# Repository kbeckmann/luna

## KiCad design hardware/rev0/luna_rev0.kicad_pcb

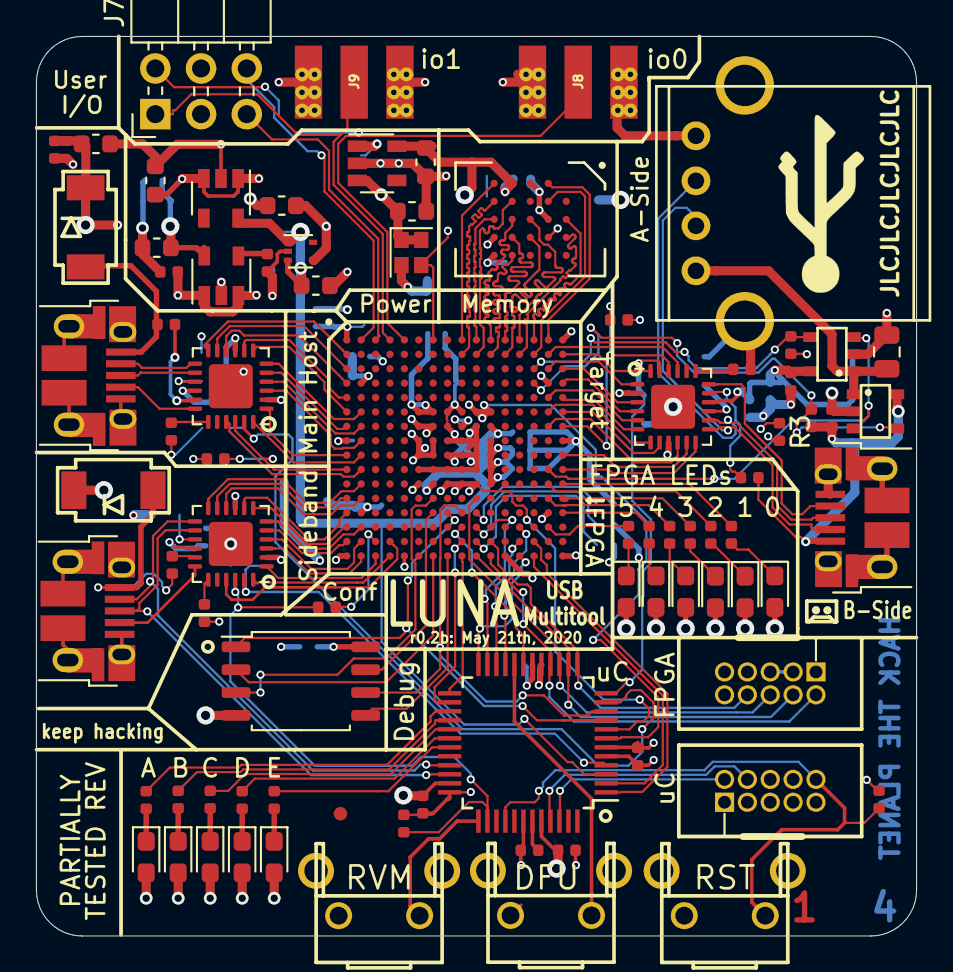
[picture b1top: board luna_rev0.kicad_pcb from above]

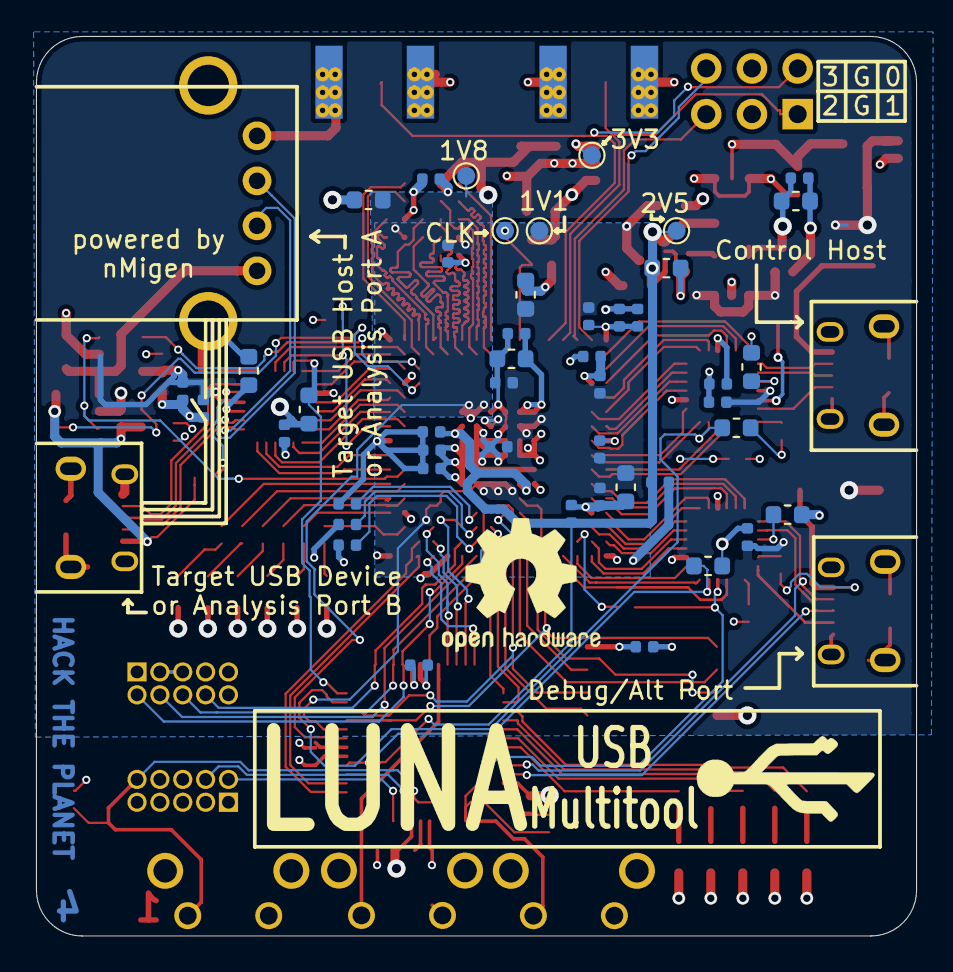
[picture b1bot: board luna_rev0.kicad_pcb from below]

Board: 4 copper layers, 48.9 x 50.0 mm, 128 parts (46 on the bottom side), 143 nets.

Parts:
C1, C2, C3, C4, C6, C20, C21: 2.2uF; C_0603_1608Metric
C5, C19, C22, C28, C29, C30, C36, C37, C42, C43, C48, C50: 1uF; C_0603_1608Metric
C7, C8, C9, C10, C11, C12, C13, C14, C15, C16, C17, C18, C23, C24, C25, C26, C27, C31, C32, C33, C34, C35, C38, C39, C40, C41, C44, C45, C46, C47, C49, C51, C54, C55: 0.1uF; C_0402_1005Metric
C52: 470pF; C_0402_1005Metric
C53: 10uF; C_0805_2012Metric
D1, D8: PMEG3050EP,115; SOD128
D2: RED; LED_0603_1608Metric_Pad1.05x0.95mm_HandSolder
D3: ORANGE; LED_0603_1608Metric_Pad1.05x0.95mm_HandSolder
D4: YELLOW; LED_0603_1608Metric_Pad1.05x0.95mm_HandSolder
D5: GREEN; LED_0603_1608Metric_Pad1.05x0.95mm_HandSolder
D6, D10, D14: BLUE; LED_0603_1608Metric_Pad1.05x0.95mm_HandSolder
D7: PURPLE; LED_0603_1608Metric_Pad1.05x0.95mm_HandSolder
D11, D13: PINK; LED_0603_1608Metric_Pad1.05x0.95mm_HandSolder
D12: WHITE; LED_0603_1608Metric_Pad1.05x0.95mm_HandSolder
FID: Fiducial_0.75mm_Mask2.25mm
IC1: ECP5-BGA256; lattice_cabga256
J1, J2, J4: USB_B_Micro; USB_Micro-B_Amphenol_10103594-0001LF_Horizontal
J3: USB_A; CONN-Amphenol-UE27AC54100
J5, J6: Conn_ARM_JTAG_SWD_10; SWD_CONNECTOR_LARGE_BOX
J7: Conn_02x02_Counter_Clockwise; PinHeader_2x03_P2.54mm_Horizontal
J8, J9: Conn_Coaxial; SMA-EDGE
R1, R2, R3, R12, R13, R14, R23, R24, R25: 10K; R_0402_1005Metric
R7, R8, R9, R10, R11, R26, R27, R28, R29, R30, R31: 330; R_0402_1005Metric
R15: 1K; R_0402_1005Metric
R16, R18, R20: 8.06k+1%; R_0402_1005Metric
R17, R19, R21: 20K; R_0402_1005Metric
R22: 15K; R_0402_1005Metric
SW1: BTN_RECOVERY; SWITCH-FSMRA
SW2: BTN_DFU; SWITCH-FSMRA
SW3: BTN_RESET; SWITCH-FSMRA
TP1, TP2, TP3, TP4, TP5: TestPoint; TestPoint_Pad_D1.0mm
U1, U12: AP22814-SOT; SOT25
U2: MIC5504-1.8YM5; SOT-23-5
U3: MIC5219-3.3YM5; SOT-23-5
U4: TCR2EE11; SOT-553
U5: MIC5504-2.5YM5; SOT-23-5
U6: ATSAMD21G18A-AUT; TQFP-48_7x7mm_P0.5mm
U7: W25Q32JVSS; SOIC-8_5.23x5.23mm_P1.27mm
U8, U9, U11: USB3343; VQFN-24-1EP_4x4mm_P0.5mm_EP2.45x2.45mm
U10: S27KS0641; BGA-24_5x5_6.0x8.0mm
Y1: DSC60xx; Crystal_SMD_2016-4Pin_2.0x1.6mm

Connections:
+1V1: C1.1, C3.1, C7.1, C9.1, C11.1, C13.1, C15.1, C17.1, C29.1, IC1.G6, IC1.G7, IC1.G9, IC1.L8, IC1.L9, IC1.L10, TP4.1, U4.4, U6.8
+1V8: C19.1, C21.1, C23.1, C25.1, IC1.F10, IC1.F11, TP2.1, U2.5, U6.7, U10.B4, U10.D1, U10.E4
+2V5: C22.1, C24.1, C26.1, C27.1, C30.1, IC1.G11, IC1.L7, TP5.1, U4.1, U4.3, U5.5, U6.3
+3V3: C2.1, C4.1, C5.1, C8.1, C10.1, C12.1, C14.1, C16.1, C18.1, C20.1, C28.1, C31.1, C32.1, C33.1, C34.1, C35.1, C39.1, C41.1, C49.1, D2.2, D3.2, D4.2, D5.2, D6.2, D7.2, D10.2, D11.2, D12.2, D13.2, D14.2, IC1.F6, IC1.F7, IC1.H6, IC1.H7, IC1.H11, IC1.J6, IC1.J7, IC1.J11, IC1.K11, IC1.L6, IC1.L11, J5.1, J6.1, R3.1, R13.2, R22.2, R23.2, R24.2, R25.1, TP3.1, U2.1, U2.3, U3.5, U5.1, U5.3, U6.6, U6.17, U6.36, U6.44, U7.8, U8.2, U8.9, U9.2, U9.9, U11.2, U11.9, Y1.1, Y1.4
+5V: C6.1, C38.1, C40.1, C44.1, C45.1, C46.1, C47.1, C54.1, D1.1, D8.1, U1.5, U3.1, U3.3, U8.16, U9.16, U11.16
/DEBUG_SPI_CLK: IC1.R13, U6.22
/DEBUG_SPI_CS: IC1.T13, U6.24
/DEBUG_SPI_MISO: IC1.P11, U6.23
/DEBUG_SPI_MOSI: IC1.P13, U6.21
/Debug & Control Connections/CLKIN_60MHZ: IC1.A7, TP1.1, Y1.3
/Debug & Control Connections/USER_IO0: IC1.A5, J7.2, J8.1
/Debug & Control Connections/USER_IO1: IC1.A4, J7.1, J9.1
/Debug & Control Connections/USER_IO2: IC1.A3, J7.5
/Debug & Control Connections/USER_IO3: IC1.A2, J7.6
/FORCE_DFU: SW2.2, U6.20
/FORCE_RECOVERY: SW1.2, U6.37
/FPGA Configuration and Dev Features/D0: IC1.T8, U7.5
/FPGA Configuration and Dev Features/D1: IC1.T7, U7.2
/FPGA Configuration and Dev Features/D2: IC1.M7, U7.3
/FPGA Configuration and Dev Features/D3: IC1.N7, U7.7
/FPGA Configuration and Dev Features/FPGA_CFG0: IC1.N10, R12.1
/FPGA Configuration and Dev Features/FPGA_CFG1: IC1.P10, R13.1
/FPGA Configuration and Dev Features/FPGA_CFG2: IC1.R10, R14.1
/FPGA Configuration and Dev Features/FPGA_CONFIG_CLK: IC1.N9, U6.10, U7.6
/FPGA Configuration and Dev Features/FPGA_DONE: IC1.P9, U6.19
/FPGA Configuration and Dev Features/FPGA_TCK: IC1.T10, J5.4, U6.14
/FPGA Configuration and Dev Features/FPGA_TDI: IC1.R11, J5.8, U6.13
/FPGA Configuration and Dev Features/FPGA_TDO: IC1.M10, J5.6, U6.15
/FPGA Configuration and Dev Features/FPGA_TMS: IC1.T11, J5.2, U6.16
/FPGA Configuration and Dev Features/UC_SWDCLK: J6.4, U6.45
/FPGA Configuration and Dev Features/UC_SWDIO: J6.2, U6.46
/FPGA Configuration and Dev Features/~CS_DI: IC1.N8, U6.9, U7.1
/FPGA Configuration and Dev Features/~FPGA_INIT: IC1.T9, U6.25
/FPGA Configuration and Dev Features/~FPGA_PROGRAM: IC1.R9, U6.26
/FULL_RESET: J6.10, R25.2, SW3.2, U6.40
/HOST_D+: J1.3, U11.14
/HOST_D-: J1.2, U11.13
/HOST_ID: J1.4, U11.18
/HOST_PHY_1V8: C50.1, U6.11, U11.23
/Host Section/HOST_DATA0: IC1.G2, U11.4
/Host Section/HOST_DATA1: IC1.G1, U11.5
/Host Section/HOST_DATA2: IC1.F2, U11.6
/Host Section/HOST_DATA3: IC1.F1, U11.7
/Host Section/HOST_DATA4: IC1.E1, U11.8
/Host Section/HOST_DATA5: IC1.D1, U11.10
/Host Section/HOST_DATA6: IC1.C1, U11.11
/Host Section/HOST_DATA7: IC1.B1, U11.12
/Host Section/HOST_DIR: IC1.J1, U11.1
/Host Section/HOST_NXT: IC1.H2, U11.3
/Host Section/HOST_PHY_CLK: IC1.K2, U11.21
/Host Section/HOST_PHY_RESET: IC1.K1, R24.1, U11.22
/Host Section/HOST_STP: IC1.J2, U11.24
/Host Section/HOST_VBUS: D1.2, J1.1, R21.1
/PROVIDE_A_PORT_VBUS: IC1.C14, R1.2, U1.4
/RAM / 1V8 Section/CLK: IC1.B14, U10.B2
/RAM / 1V8 Section/RAM_DQ0: IC1.A11, U10.D3
/RAM / 1V8 Section/RAM_DQ1: IC1.B10, U10.D2
/RAM / 1V8 Section/RAM_DQ2: IC1.B12, U10.C4
/RAM / 1V8 Section/RAM_DQ3: IC1.A12, U10.D4
/RAM / 1V8 Section/RAM_DQ4: IC1.B11, U10.D5
/RAM / 1V8 Section/RAM_DQ5: IC1.A10, U10.E3
/RAM / 1V8 Section/RAM_DQ6: IC1.B9, U10.E2
/RAM / 1V8 Section/RAM_DQ7: IC1.A9, U10.E1
/RAM / 1V8 Section/RAM_RWDS: IC1.A13, U10.C3
/RAM / 1V8 Section/~CLK: IC1.A15, U10.B1
/RAM / 1V8 Section/~CS: IC1.A14, U10.A3
/RAM / 1V8 Section/~RESET: IC1.B13, U10.A4
/Right side indicators/D0: IC1.P15, R31.2
/Right side indicators/D1: IC1.N16, R30.2
/Right side indicators/D2: IC1.M15, R29.2
/Right side indicators/D3: IC1.M16, R28.2
/Right side indicators/D4: IC1.L15, R27.2
/Right side indicators/D5: IC1.L16, R26.2
/SIDEBAND_D+: J2.3, U6.34, U8.14
/SIDEBAND_D-: J2.2, U6.33, U8.13
/SIDEBAND_ID: J2.4, U8.18
/SIDEBAND_PHY_1V8: C37.1, U6.4, U8.23
/SIDEBAND_VBUS: D8.2, J2.1, R17.1
/Sideband Section/SIDEBAND_DATA0: IC1.R2, U8.4
/Sideband Section/SIDEBAND_DATA1: IC1.R1, U8.5
/Sideband Section/SIDEBAND_DATA2: IC1.P2, U8.6
/Sideband Section/SIDEBAND_DATA3: IC1.P1, U8.7
/Sideband Section/SIDEBAND_DATA4: IC1.N1, U8.8
/Sideband Section/SIDEBAND_DATA5: IC1.M2, U8.10
/Sideband Section/SIDEBAND_DATA6: IC1.M1, U8.11
/Sideband Section/SIDEBAND_DATA7: IC1.L2, U8.12
/Sideband Section/SIDEBAND_DIR: IC1.T3, U8.1
/Sideband Section/SIDEBAND_NXT: IC1.T2, U8.3
/Sideband Section/SIDEBAND_PHY_CLK: IC1.R4, U8.21
/Sideband Section/SIDEBAND_STP: IC1.T4, U8.24
/TARGET_D+: J3.3, J4.3, U9.14
/TARGET_D-: J3.2, J4.2, U9.13
/TARGET_FAULT: IC1.K15, R3.2, U1.3, U12.3
/TARGET_ID: J4.4, U9.18
/TARGET_PHY_1V8: C43.1, U6.12, U9.23
/TARGET_VBUS_IN: C55.1, J4.1, R2.2, R19.1, U12.5
/TARGET_VBUS_OUT: C53.2, J3.1, U1.1, U12.1
/Target Section/TARGET_DATA0: IC1.D16, U9.4
/Target Section/TARGET_DATA1: IC1.E15, U9.5
/Target Section/TARGET_DATA2: IC1.E16, U9.6
/Target Section/TARGET_DATA3: IC1.F15, U9.7
/Target Section/TARGET_DATA4: IC1.F16, U9.8
/Target Section/TARGET_DATA5: IC1.G15, U9.10
/Target Section/TARGET_DATA6: IC1.J16, U9.11
/Target Section/TARGET_DATA7: IC1.K16, U9.12
/Target Section/TARGET_PHY_CLK: IC1.B15, U9.21
/Target Section/TARGET_PHY_DIR: IC1.C15, U9.1
/Target Section/TARGET_PHY_NXT: IC1.C16, U9.3
/Target Section/TARGET_PHY_RESET: IC1.G16, R23.1, U9.22
/Target Section/TARGET_PHY_STP: IC1.B16, U9.24
/UC_RX_FPGA_TX: IC1.T14, U6.2
/UC_TX_FPGA_RX: IC1.R14, U6.1
/USB_INHIBIT: R15.1, R22.1, U6.38, U8.22
/VBUS_PASSTHROUGH_EN: IC1.D14, R2.1, U12.4
GND: C1.2, C2.2, C3.2, C4.2, C5.2, C6.2, C7.2, C8.2, C9.2, C10.2, C11.2, C12.2, C13.2, C14.2, C15.2, C16.2, C17.2, C18.2, C19.2, C20.2, C21.2, C22.2, C23.2, C24.2, C25.2, C26.2, C27.2, C28.2, C29.2, C30.2, C31.2, C32.2, C33.2, C34.2, C35.2, C36.2, C37.2, C38.2, C39.2, C40.2, C41.2, C42.2, C43.2, C44.2, C45.2, C46.2, C47.2, C48.2, C49.2, C50.2, C51.2, C52.2, C53.1, C54.2, C55.2, IC1.A1, IC1.A16, IC1.D2, IC1.D15, IC1.F8, IC1.F9, IC1.G8, IC1.G10, IC1.H1, IC1.H8, IC1.H9, IC1.H10, IC1.H16, IC1.J8, IC1.J9, IC1.J10, IC1.K6, IC1.K7, IC1.K8, IC1.K9, IC1.K10, IC1.N2, IC1.N15, IC1.T1, IC1.T5, IC1.T12, IC1.T16, J1.5, J1.6, J2.5, J2.6, J3.4, J3.5, J4.5, J4.6, J5.3, J5.5, J5.9, J6.3, J6.5, J6.9, J7.3, J7.4, J8.2, J9.2, R1.1, R12.2, R14.2, R16.1, R18.1, R20.1, SW1.1, SW2.1, SW3.1, U1.2, U2.2, U3.2, U4.2, U5.2, U6.5, U6.18, U6.35, U6.42, U7.4, U8.25, U9.25, U10.B3, U10.C1, U10.E5, U11.25, U12.2, Y1.2
unnamed: C36.1, U8.15
unnamed: C42.1, U9.15
unnamed: C48.1, U11.15
unnamed: C51.1, U6.43
unnamed: C52.1, U3.4
unnamed: D2.1, R26.1
unnamed: D3.1, R27.1
unnamed: D4.1, R28.1
unnamed: D5.1, R29.1
unnamed: D6.1, R30.1
unnamed: D7.1, R31.1
unnamed: D10.1, R7.1
unnamed: D11.1, R8.1
unnamed: D12.1, R9.1
unnamed: D13.1, R10.1
unnamed: D14.1, R11.1
unnamed: IC1.R3, R15.2
unnamed: R7.2, U6.27
unnamed: R8.2, U6.28
unnamed: R9.2, U6.29
unnamed: R10.2, U6.30
unnamed: R11.2, U6.31
unnamed: R16.2, U8.19
unnamed: R17.2, U8.17
unnamed: R18.2, U9.19
unnamed: R19.2, U9.17
unnamed: R20.2, U11.19
unnamed: R21.2, U11.17

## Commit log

2020-05-21 Update version and add gerbers
2020-06-28 WIP: Bring up pergola
    Does not enumerate for some reason.
2020-06-28 Add sigrok trace of failed enumeration
2020-06-28 Add capture at 100MS/s
2020-06-28 Update with a proper signal capture
2020-06-29 Update sigrok with 400MHz capture
2020-07-02 Add traces
2020-07-02 Add annotations of glitches
2020-07-02 Swap clocks
    Works worse/not at all now. But at least it's the same as orange crab.
2020-07-09 apollo: move to using the OpenMoko VID/PID for Apollo
2020-07-09 gateware.analyzer: update analyzer to use fast USB2 transport
2020-07-09 gateware.gateware_phy: add support for non-NRZI/bitstuff modes
    This enables the gateware PHY to be used in e.g. Host modes.
2020-07-09 gateware.platform: TinyFPGA Bx: use PLL to generate 12M + 48M clocks
2020-07-09 gateware.usb: add a premade CDC-ACM device type
2020-07-09 platform.lambdaconcept: add ECPIX-5 as a supported board
2020-07-09 hardware: adopt OSHWA convention for SPI signal names
    https://www.oshwa.org/a-resolution-to-redefine-spi-signal-names
2020-07-09 docs: add basic docs for running LUNA on your own hardware
2020-07-09 platform.lambdaconcept: pull in latest ECPIX-5 mappings
2020-07-09 platform.lambdaconcept: add a small disclaimer for the ECPIX-5
2020-07-09 gateware.platform: correctly constrain iCEBreaker clocks
2020-07-09 Pull in ECP5PLL from pergola
    Things work now!
2020-07-09 gateware.platform: orangecrab fixes and iCEBreaker unofficial platform
2020-07-12 pergola: Initial bringup
2020-07-12 pergola: Add basic uart support
2020-07-12 pergola: Update tinyusb submodule

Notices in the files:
hardware/rev0/luna_rev0.kicad_pcb:
Copyright 2019-2020 Great Scott Gadgets
Licensed under the CERN-OHL-P v2
